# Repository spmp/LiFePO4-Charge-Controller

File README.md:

LiFePO4 Charge Controller
=========================

This project is for a fully automatic
_LiFePO4_ battery charger for my, utilising the HP Blade power supply ESP-120 as power source, and fully integrated with a Cell Top Module (CTM) Battery Management System (BMS). The _charger_ is essentially a battery monitor and manager that also charges when power is available to the vehicle.

Principal of operation
----------------------
LiFePO4 batteries have a relatively simple charging profile:

 * Charge at constant current until the maximum cell voltage is just below the balancing voltage
 * Vary charge voltage ensuring the maximum cell voltage is (just) below balancing voltage until the charge current is at or below 1A
 * Once charge current is at or below 1A charge at 1A until all cells are balancing
 
### Overview

### Charge control
Thanks to the efforts of a German group the ESP-120 is well documented with a known and stable voltage control from 30-53V with positive voltage into a trim-pot pin, and 53-63V with a slight negative voltage to this pin. There is an inverse relationship between voltage at the pot, and the supplies output voltage:
```
~5Vin => 30Vout
 0Vin => 53Vout
```
To operate as a charger two (or more) PSU's are connected in series which is possible as the DC output is isolated from
the case.
To achieve constant current charging, the voltage of the supplies is brought up slowly by modifying (decreasing) Vin 
whilst monitoring the current until the desired current is reached.

Not all PSU's in series need to modify their output voltage in order to achieve fine grained charge control. In my case one PSU has a varying voltage, and one does not.
The PSU's with a varying voltage are modified by removing the trim-pot and cutting/modding traces at the output plug to allow the signals to be routed from external connector.

The PSU's are protected by a large external diode (75A, 200V).

### Cell Top Modules
Each battery cell has a CTM across it which:
 * Measures cell voltage
 * Measures cell temperature
 * Switches on a 1A load once `Vbalance` is reached

The CTM's are connected in a daisy chain and communicate via serial with the cell top monitor. The CTM state's are found by sending an initialisation message to the first CTM, which adds its state to the message and passes it to the next CTM etc. until finally the packet with all cell states arrives back at the monitor. 

## Project iterations
1.  **Mark I: Proof of concept using onboard** (Done)

    - Construction on breadboard
    - Powered off the PSU power GND - 12V via an LM7805, so has common ground with Cycle Analyst
    - shunt and differential opamp via built in 10bit ADC for current measurement
    - 100:1 resistor divider via 10bit ADC for output voltage measurement
    - Output is a PWM based 'DAC' to a fet/transistor between two pot's setting max/min voltage.
    - Output/input via isolated serial interface.
  
2.  **Mark II: further improvements** (Done)
    - Impliment isolated I2C to PSU controllers for PSON and current measurement.
    - Check PSU current VS shunt current, once verified they are the same with similar reliability, discontinue use of shunt.
    - Implement software USART for Rx only to receive SOC etc. from the cycle analyst
    - Assess whether external DAC's and ADC's are necessary.
    - Likely that external ADC will be, so use it.
    - Investigate and implement different charging strategies.
    - LCD?
    - BMS integration
  
3.  **Mark III: Integrated controller** (In progress)
    - ESP32 platform, on separate board as PSU's so can run independently
    - Arduino codebase for greater platform independence and collaboration
    - Integrated CTM monitor
    - Custom PSU plug boards.
        1. Modified PSU for varying voltage output
        2. Unmodified PSU
        3. Boards plug together on edges for stackability
    - Voltage control via I2C DAC
    - Current measurement from external shunt
        - Optional current measurement on PSU plug board
    - Voltage measurement at battery terminal
    - WiFi and Bluetooth interface
    - Optional I2C display interface
    
Repo layout
-----------
```
.
├── code            Charge controller logic
│   └── AVR-lib     General AVR libraries. Should be a submodule
│       └── lib
├── doc             Documents relating to the ESP-120/HP3KW
├── pcb             Output PCB files
└── schematic       Schematic
```

The code is written in C++/Arduino using [PlatformIO], ideally exporting to Makefile.

The schematic and PCB layout are done in [Kicad]

Inputs:
-------
 **Current:** 
   Current will be measured using an external 75mV shunt and an op-amp. As the battery and the controller share the same ground there is no need to use a differential op-amp. 
   This will be read by an internal (to the ESP-32) 12bit SAR ADC using the internal 1.1`Vref`.
   Current measurements can also be taken from the PSU via I2C.
   
 **Battery Voltage:**
   Battery voltage will be measured via a 100k:1k resistor divider network protected with a zener diode. A dedicated `Vsense` lead will be attached to the positive battery terminal to avoid voltage drops in wires and diodes influencing the voltage.
   This will be read by an internal (to the ESP-32) 12bit SAR ADC using the internal 1.1`Vref`.
   
 **PSU State:**
   The PSU state can be inspected via isolated I2C, and returns the following and more:
   
   - Line voltage
   - Output current
   - Temperature
   
 **CTM:**
   CTM state will be inspected via isolated serial, and gives us the following per cell:
   
   - Cell voltage
   - Cell temperature
   - Cell state
     - Balancing
     - Over voltage
     - Over temperature
   
Outputs:
--------
 **Vin:**
   The PSU control voltage, `Vin` will be controlled via I2C DAC via an inverting op-amp to ensure the power on state is high.
      
 **Serial:**
   Debugging and logging will be via serial
 
 **I2C Display:**
   An (optional) I2C display will show the per cell voltage and other state information
   
 **LED's and stuff:**
   - Blinking light (things alive)
   - Charging
   - Complete
   - State of charge bar graph for in the window 8)
   - Even better would be EL wire or tape on the exterior.
  
 **Phone App:**
   An Android app using Bluetooth would be the ideal solution for greatest versatility

Power supply modifications
--------------------------
In order for the PSU's to be variable voltage some minor modifications need to be made:

### Trimpot, `Vin`
A trimpot needs to be removed and wires attached as `Vin`:
Remove surrounding plugs, clear off silicoln blob, and heat it up any way yo can 8)

### Interface board
The _interface board_, the PCB with the external power and data plug, needs to be modified such that we can get the 12V out, and `Vin` in, whilst maintaining `PSON` and `I2C` functionality:

### 12V supply
**Note:** The 12V supply may not be required.

12V is most easily tapped from the left hand leg of a diode on the secondary power board as shown below:

PCB's and circuit considerations
--------------------------------

[platformIO]: http://platformio.org/
[kicad]: http://kicad-pcb.org/

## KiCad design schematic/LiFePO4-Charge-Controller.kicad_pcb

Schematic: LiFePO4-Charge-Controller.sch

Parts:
CI1a1, CI1c1, CI2a1, CI2c1, CI3a1: 100nF
CI1b1, CI1d1, CI2b1, CI2d1, CI3b1: 1uF
CINA1: 100nF
CV1: 10pF
Cpwm1: 300nF
Dled1, Dled2: LED
OC1, OC2, OC3: PC817; DIP4
PI1, PI2, PI2C1: I2C
PIRS232: RS232
Popto1, Popto2, Popto3: opto
Pshunt1: differential
Pvolt1: Gnd PWM 12V B+
Qpnp1: NPN
RI1scl1, RI1sda1, RI2scl1, RI2sda1: 5k
RI2Cscl1, RI2Csda1: 1.8k
RVR1a1, RVR1b1: 99k
RVR2a1, RVR2b1: 1k
Rg1: 5k
Rled1: 1k
Rled2: 1K
Ropto1, Ropto2, Ropto3: 1k
Rpwm1: 120
RpwmDrv1: 560
UI1, UI2: SI8400; MODULE
UINA1: AD8236; MODULE
UIR1: SI8400; MODULE
UuC1: ARDUINO_Nano; DIL20

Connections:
5v: CI1a1.1, CI1b1.1, CI2a1.1, CI2b1.1, CI3a1.2, CI3b1.2, PI2C1.1, RI2Cscl1.1, RI2Csda1.1, Rpwm1.2, UI1.8, UI2.8, UINA1.8 (+VS), UIR1.1, UuC1.12
D3: Ropto1.1, UuC1.21
D5: Ropto2.1, UuC1.23
D6: Ropto3.1, UuC1.24
Gnd: CI1a1.2, CI1b1.2, CI2a1.2, CI2b1.2, CI3a1.1, CI3b1.1, CINA1.2, CV1.2, Cpwm1.2, Dled1.2 (K), Dled2.2 (K), OC1.2, OC2.2, OC3.2, PI2C1.4, Pvolt1.4, Qpnp1.1 (E), RVR2a1.2, RVR2b1.2, UI1.5, UI2.5, UINA1.5 (-VS), UINA1.6 (REF), UIR1.4, UuC1.14, UuC1.19
I2C1_GND: CI1c1.2, CI1d1.2, PI1.4, UI1.4
I2C2_GND: CI2c1.2, CI2d1.2, PI2.4, UI2.4
unnamed: UIR1.2, UuC1.17
unnamed: UIR1.3, UuC1.16
unnamed: PI1.3, RI1scl1.2, UI1.3
unnamed: PI1.2, RI1sda1.2, UI1.2
unnamed: PI2.2, RI2sda1.2, UI2.2
unnamed: CV1.1, RVR1a1.2, RVR1b1.2, RVR2a1.1, RVR2b1.1, UuC1.4
unnamed: PIRS232.3, UIR1.6
unnamed: PIRS232.2, UIR1.7
unnamed: PIRS232.1, UIR1.8
unnamed: PI2.3, RI2scl1.2, UI2.3
unnamed: OC1.4, Popto1.1
unnamed: OC3.4, Popto3.1
unnamed: OC3.1, Ropto3.2
unnamed: OC2.3, Popto2.2 (PM)
unnamed: OC2.4, Popto2.1
unnamed: OC2.1, Ropto2.2
unnamed: OC1.3, Popto1.2 (PM)
unnamed: OC3.3, Popto3.2 (PM)
unnamed: OC1.1, Ropto1.2
unnamed: Cpwm1.1, Pvolt1.3, Qpnp1.3 (C), Rpwm1.1
unnamed: Qpnp1.2 (B), RpwmDrv1.2
unnamed: Dled1.1 (A), Rled1.2
unnamed: Dled2.1 (A), Rled2.2
unnamed: RpwmDrv1.1, UuC1.27
unnamed: Rled2.1, UuC1.30
unnamed: Rled1.1, UuC1.29
unnamed: Rg1.1, Rg1.2, UINA1.2 (RG)
unnamed: UINA1.7 (Vout), UuC1.5
unnamed: Pshunt1.2 (PM), UINA1.4 (+IN)
unnamed: Pshunt1.1, UINA1.1 (-IN)
unnamed: Rg1.3, UINA1.3 (RG)
unnamed: Pvolt1.2, UuC1.15
unnamed: CI2c1.1, CI2d1.1, PI2.1, RI2scl1.1, RI2sda1.1, UI2.1
unnamed: CI1c1.1, CI1d1.1, PI1.1, RI1scl1.1, RI1sda1.1, UI1.1
unnamed: PI2C1.3, RI2Csda1.2, UI1.7, UI2.7, UuC1.8
unnamed: PI2C1.2, RI2Cscl1.2, UI1.6, UI2.6, UuC1.9
unnamed: Pvolt1.1, RVR1a1.1, RVR1b1.1
RS232_GND: PIRS232.4, UIR1.5

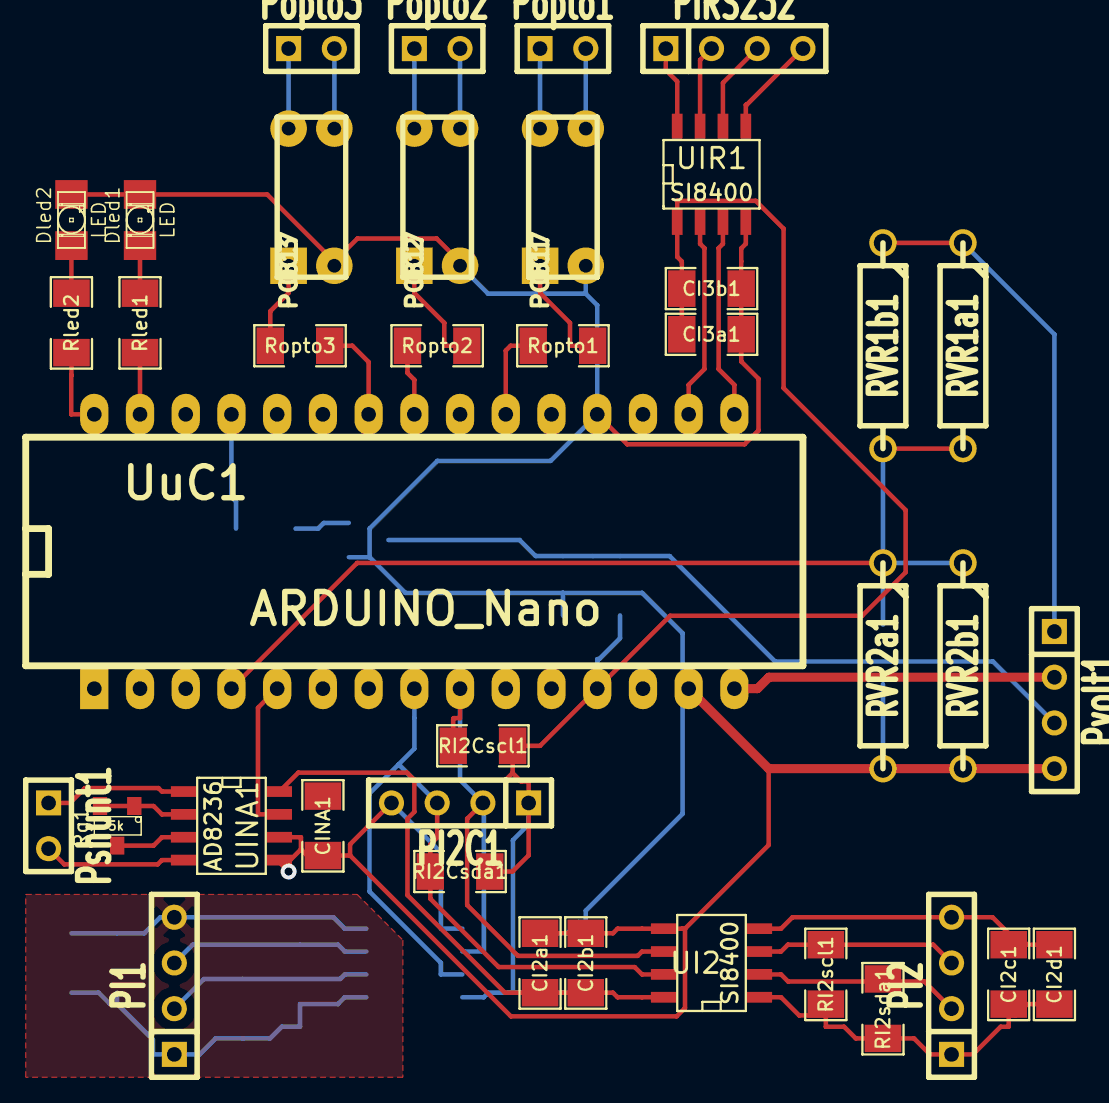
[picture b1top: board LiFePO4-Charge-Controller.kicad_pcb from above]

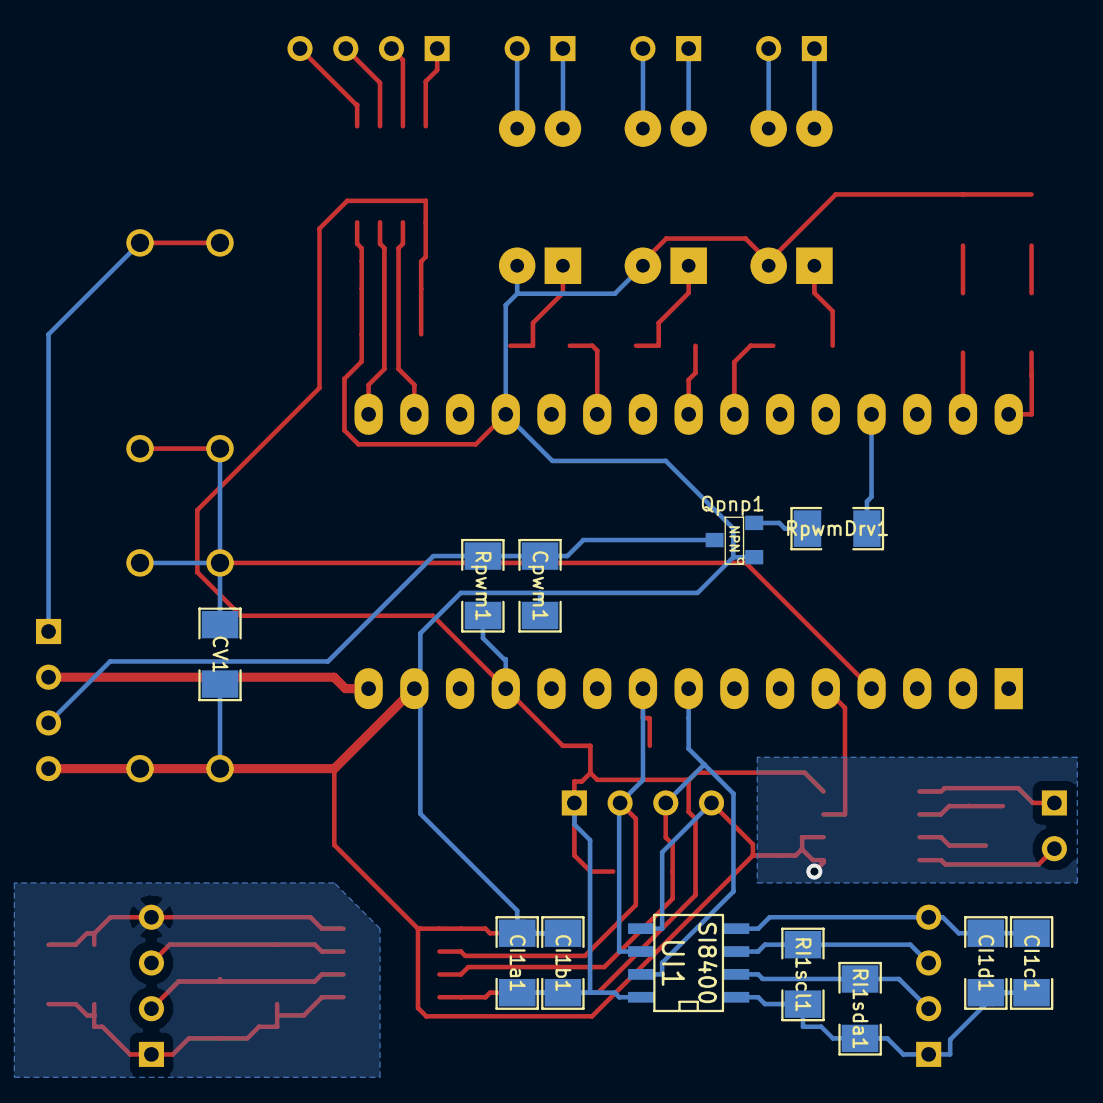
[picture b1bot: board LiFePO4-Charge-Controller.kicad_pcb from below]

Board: 2 copper layers, 51 parts (12 on the bottom side), 45 nets.

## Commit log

2014-07-21 Initial code, and subrepo of AVR-lib where most of the work is going on ATM
2014-07-21 brr!
2014-07-21 brr again
2014-07-22 modified hardware.{h,c}, main.c and Makefile (to reflect new pathnames). Lets see if it all works 8)
2014-07-22 Working code with basic USART interaction for checking voltage and setting PWM. NOTE: PWM as DAC use series 130 ohm (using 330 ohm) reistor with 10uF cap to ground as output
2014-07-22 getting ready for PID
2014-07-23 A fairly stable oscillating system thingee
2014-07-24 random place to commit, working on process control and hardware
2014-07-24 process_control.c, calculate_outputs, notchargin case 0 done as far as can be expected with no real hardware to work on
2014-07-24 process_control.c, calculate_outputs, Bulk charge case 1 done as far as can be expected with no real hardware to work on
2014-07-24 process_control.c, calculate_outputs done! what a huuuuge... dont want to say mess, but its massive!
2014-07-25 Logging and serial interface (Command.c) modifierd
2014-07-28 Begin schematic and PCB, making account for multiple posibilities... oh joy. TODO: Reverse order of PID and pwm reduction to be inverted
2014-07-29 Autoraouted board b4 contraction
2014-07-29 Smaller, w solid fill
2014-07-29 PCB satisfactory, bit of a mess around I2C, but will go with it
2014-07-30 PWM/PID code corrected. PCB: In-Amp pad (module) corrected. Board done.
2014-08-15 moving to another computer. PCB: Moving to new version of Kicad, and making resistors SMD etc
2014-10-19 Modified schematic to incorporate fix on PWM output, still working on non tracked test code
2014-12-06 Basic working solution
2014-12-06 Merged changes from testing
2014-12-06 Further corrections from merge
2014-12-06 Adding ESP120.{c,h}
2015-05-05 modified for new I2C address. Having issues with I2C reset and continue
2015-05-06 I2C adress modified again for more robust adressing (hardware)
2015-05-23 Completing code for PIDtype 2 and 3: Wait timer and float timer
2015-05-23 fixing more code... not working somehow
2015-05-23 Fixed PIDtype 2 problems. Fixed commands to return value on null input. Fixed Ah count.
2015-05-23 Getting closer to float charge. Need current and voltage control
2015-05-23 Fixed Float pwm problem by adding float current control - Needs verification. Added limits detection and correction (stop all)
2015-05-24 Fixed float. made logging nice.
2015-05-24 Fix indenting and change logging order
2016-10-17 Add some documents
2017-09-28 Beginnings of VII
2017-09-28 Update readme, especially with images of PSU modifications
2017-11-01 Who knows where this has ended up, but this branch is done, and should not be used. Deleteme!
2017-11-01 Initial commit to BMS branch, cleanup and whatnot
2017-11-01 Add subrepos
2017-11-01 UPdate AVR-lib version
2017-11-02 Update voltage limits, and process numbers
2017-11-04 Attempt to fix exit from CV. Update pip proportions
2018-01-04 Minor changes, currently working with BMSMasterController
